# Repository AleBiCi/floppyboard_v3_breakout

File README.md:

# floppyboard_v3_breakout
Breakout board design for FloppyBoard v3.1

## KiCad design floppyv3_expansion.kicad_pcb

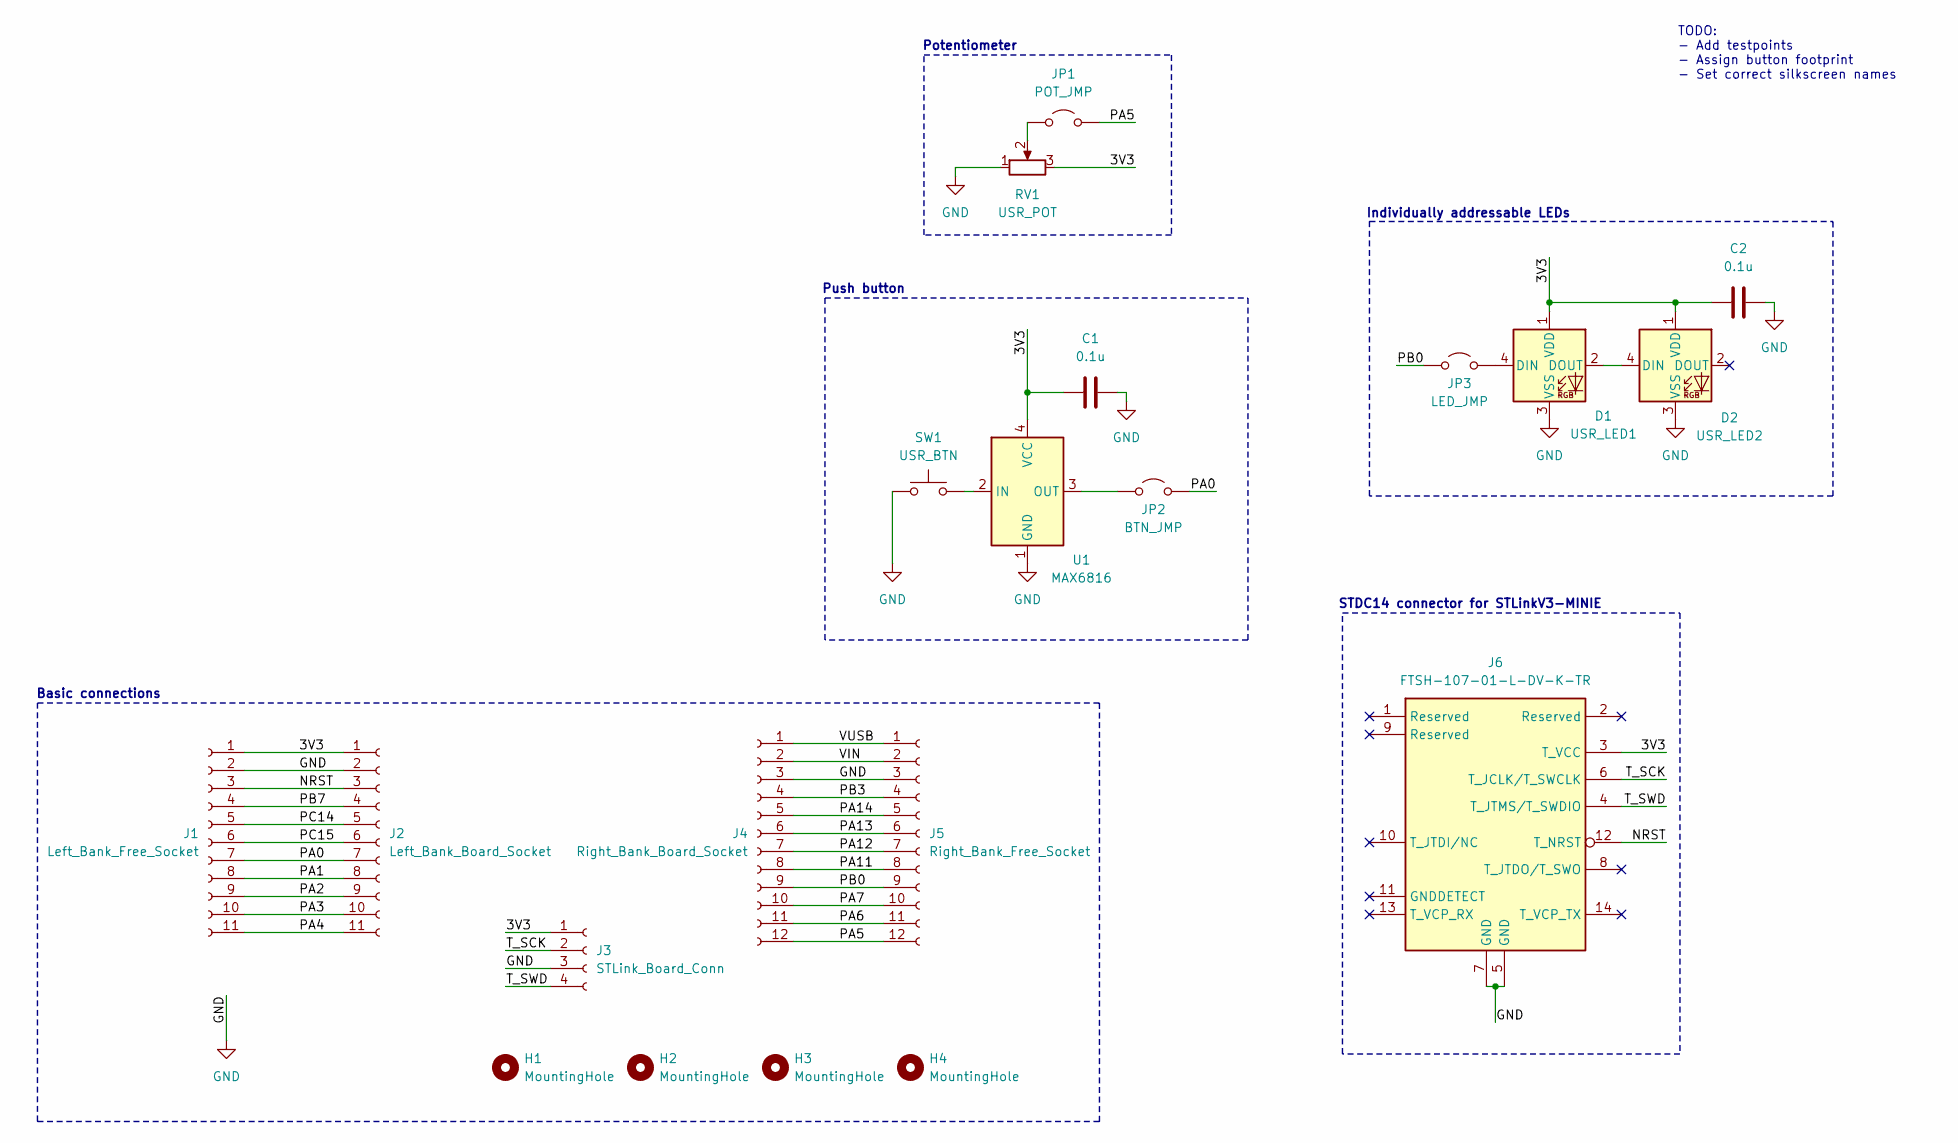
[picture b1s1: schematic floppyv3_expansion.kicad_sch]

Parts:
C1, C2: 0.1u; C_0805_2012Metric
D1: USR_LED1; LED_WS2812B_PLCC4_5.0x5.0mm_P3.2mm
D2: USR_LED2; LED_WS2812B_PLCC4_5.0x5.0mm_P3.2mm
H1, H2, H3, H4: MountingHole; MountingHole_2.2mm_M2_Pad_Via
J1: Left_Bank_Free_Socket; PinSocket_1x11_P2.54mm_Vertical
J2: Left_Bank_Board_Socket; PinSocket_1x11_P2.54mm_Vertical
J3: STLink_Board_Conn; PinSocket_1x04_P2.54mm_Vertical
J4: Right_Bank_Board_Socket; PinSocket_1x12_P2.54mm_Vertical
J5: Right_Bank_Free_Socket; PinSocket_1x12_P2.54mm_Vertical
J6: FTSH-107-01-L-DV-K-TR; SAMTEC_FTSH-107-01-L-DV-K-TR; Mouser Part Number 200-FTSH10701LDVKTR
JP1: POT_JMP; PinHeader_1x02_P2.54mm_Vertical
JP2: BTN_JMP; PinHeader_1x02_P2.54mm_Vertical
JP3: LED_JMP; PinHeader_1x02_P2.54mm_Vertical
RV1: USR_POT; Potentiometer_Alps_RK09K_Single_Vertical
SW1: USR_BTN; SW_PUSH-12mm
U1: MAX6816; SOT-143

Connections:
/3V3: C1.1, C2.1, D1.1 (VDD), D2.1 (VDD), J1.1, J2.1, J3.1, J6.3 (T_VCC), RV1.3, U1.4 (VCC)
/NRST: J1.3, J2.3, J6.12 (T_NRST)
/PA0: J1.7, J2.7, JP2.2 (B)
/PA1: J1.8, J2.8
/PA2: J1.9, J2.9
/PA3: J1.10, J2.10
/PA4: J1.11, J2.11
/PA5: J4.12, J5.12, JP1.2 (B)
/PA6: J4.11, J5.11
/PA7: J4.10, J5.10
/PA11: J4.8, J5.8
/PA12: J4.7, J5.7
/PA13: J4.6, J5.6
/PA14: J4.5, J5.5
/PB0: J4.9, J5.9, JP3.1 (A)
/PB3: J4.4, J5.4
/PB7: J1.4, J2.4
/PC14: J1.5, J2.5
/PC15: J1.6, J2.6
/T_SCK: J3.2, J6.6 (T_JCLK/T_SWCLK)
/T_SWD: J3.4, J6.4 (T_JTMS/T_SWDIO)
/VIN: J4.2, J5.2
/VUSB: J4.1, J5.1
GND: C1.2, C2.2, D1.3 (VSS), D2.3 (VSS), J1.2, J2.2, J3.3, J4.3, J5.3, J6.5 (GND), J6.7 (GND), RV1.1, SW1.1, U1.1 (GND)
unnamed: D1.4 (DIN), JP3.2 (B)
unnamed: D1.2 (DOUT), D2.4 (DIN)
unnamed: JP1.1 (A), RV1.2
unnamed: JP2.1 (A), U1.3 (OUT)
unnamed: SW1.2, U1.2 (IN)

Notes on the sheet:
Push button
STDC14 connector for STLinkV3-MINIE
Basic connections
Potentiometer
TODO: - Add testpoints - Assign button footprint - Set correct silkscreen names
Individually addressable LEDs

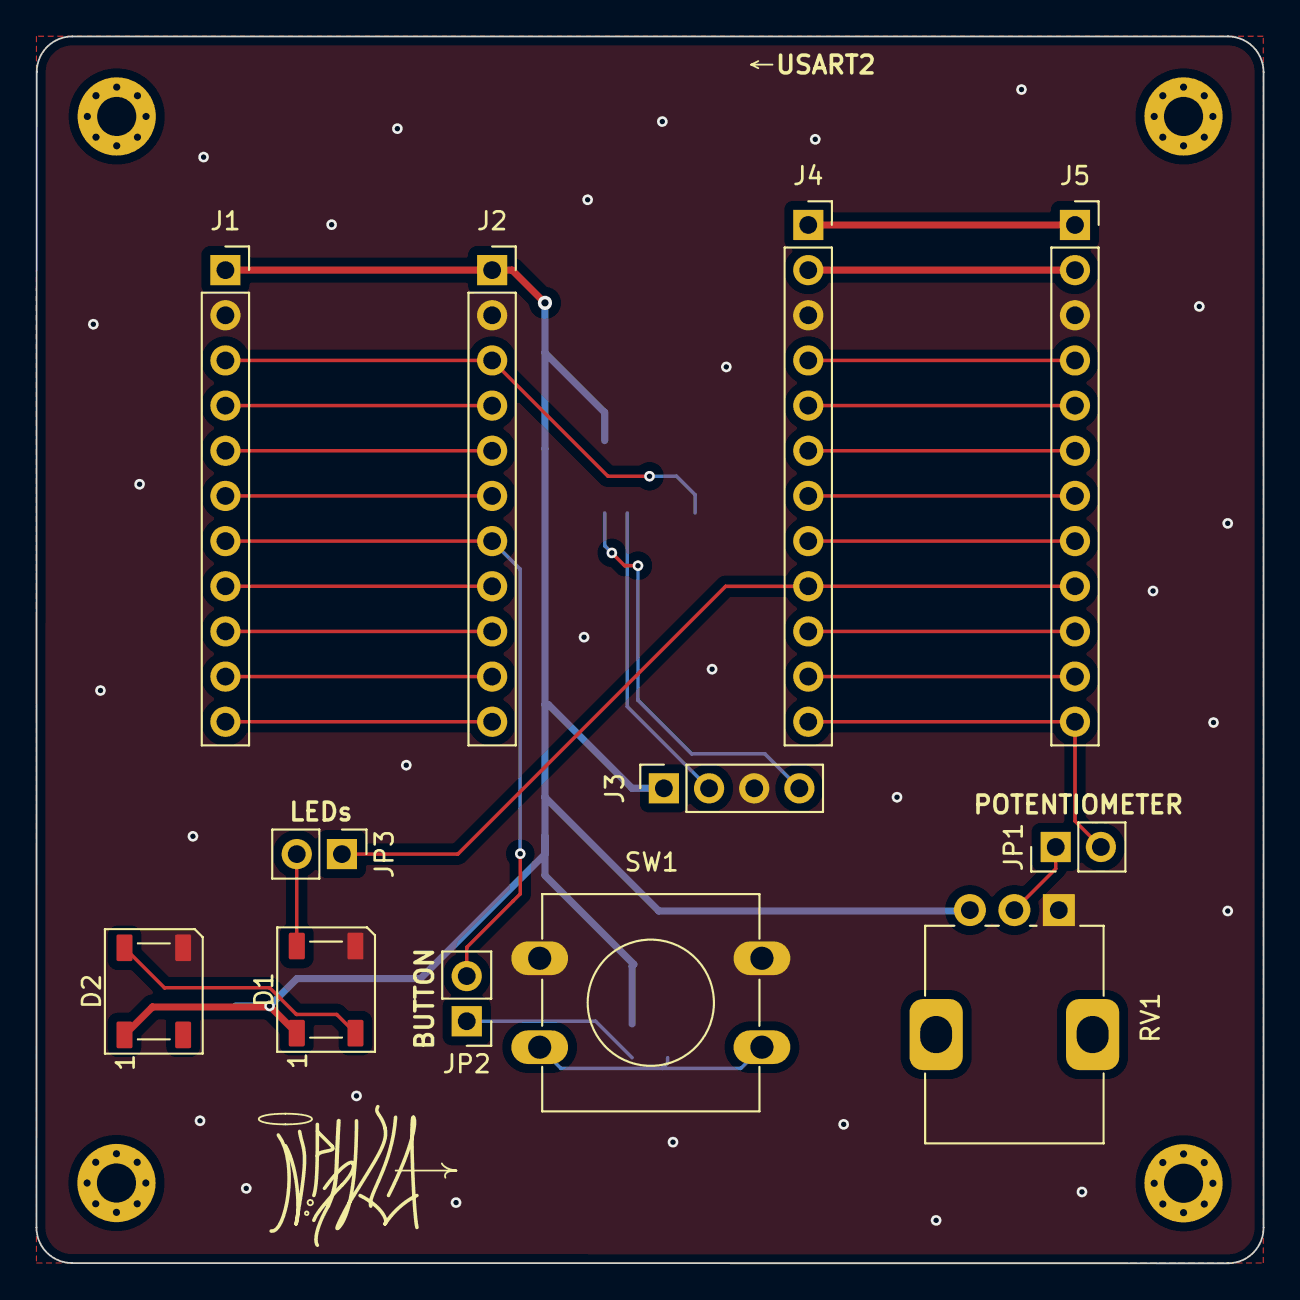
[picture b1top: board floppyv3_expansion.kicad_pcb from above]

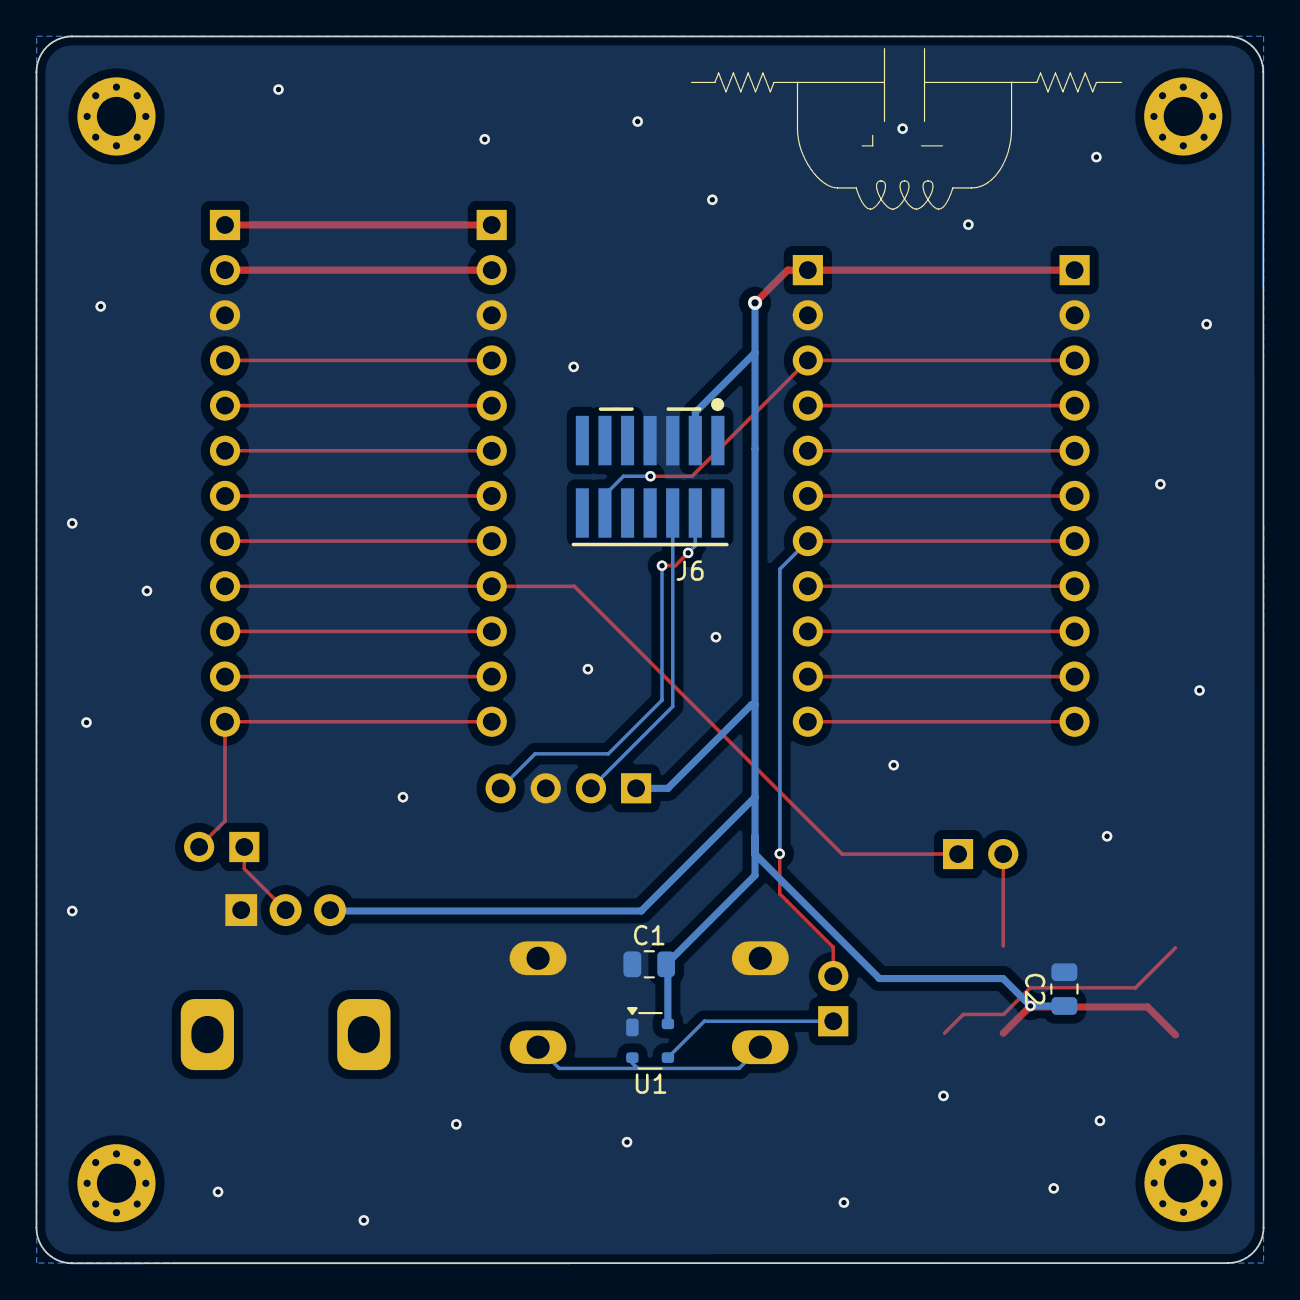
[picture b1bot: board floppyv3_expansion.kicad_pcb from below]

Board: 2 copper layers, 69.0 x 69.0 mm, 20 parts (4 on the bottom side), 29 nets.

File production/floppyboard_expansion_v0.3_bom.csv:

Designator,Footprint,Quantity,Value,LCSC Part #
"C1, C2",0805,2,0.1u,
D1,LED_WS2812B_PLCC4_5.0x5.0mm_P3.2mm,1,USR_LED1,
D2,LED_WS2812B_PLCC4_5.0x5.0mm_P3.2mm,1,USR_LED2,
J1,PinSocket_1x11_P2.54mm_Vertical,1,Left_Bank_Free_Socket,
J2,PinSocket_1x11_P2.54mm_Vertical,1,Left_Bank_Board_Socket,
J3,PinSocket_1x04_P2.54mm_Vertical,1,STLink_Board_Conn,
J4,PinSocket_1x12_P2.54mm_Vertical,1,Right_Bank_Board_Socket,
J5,PinSocket_1x12_P2.54mm_Vertical,1,Right_Bank_Free_Socket,
J6,SAMTEC_FTSH-107-01-L-DV-K-TR,1,FTSH-107-01-L-DV-K-TR,
JP1,PinHeader_1x02_P2.54mm_Vertical,1,POT_JMP,
JP2,PinHeader_1x02_P2.54mm_Vertical,1,BTN_JMP,
JP3,PinHeader_1x02_P2.54mm_Vertical,1,LED_JMP,
RV1,Potentiometer_Alps_RK09K_Single_Vertical,1,USR_POT,
SW1,SW_PUSH-12mm,1,USR_BTN,
U1,SOT-143,1,MAX6816,

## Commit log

2025-11-26 Populated repo
2025-11-29 Almost finished v0.1
2025-11-29 Started layout
2025-12-01 Added .gitignore
2025-12-01 Removed .DS_Store
2025-12-01 Starting to layout components
2025-12-02 Further improvements to layout and schematic
2025-12-02 Added final (?) touches to layout
2025-12-10 New production files generated, BOM not fully compatible w/ LCSC
2025-12-10 Updated to production version
